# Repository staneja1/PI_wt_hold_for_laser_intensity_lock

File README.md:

# PI with integrator hold for intensity lock

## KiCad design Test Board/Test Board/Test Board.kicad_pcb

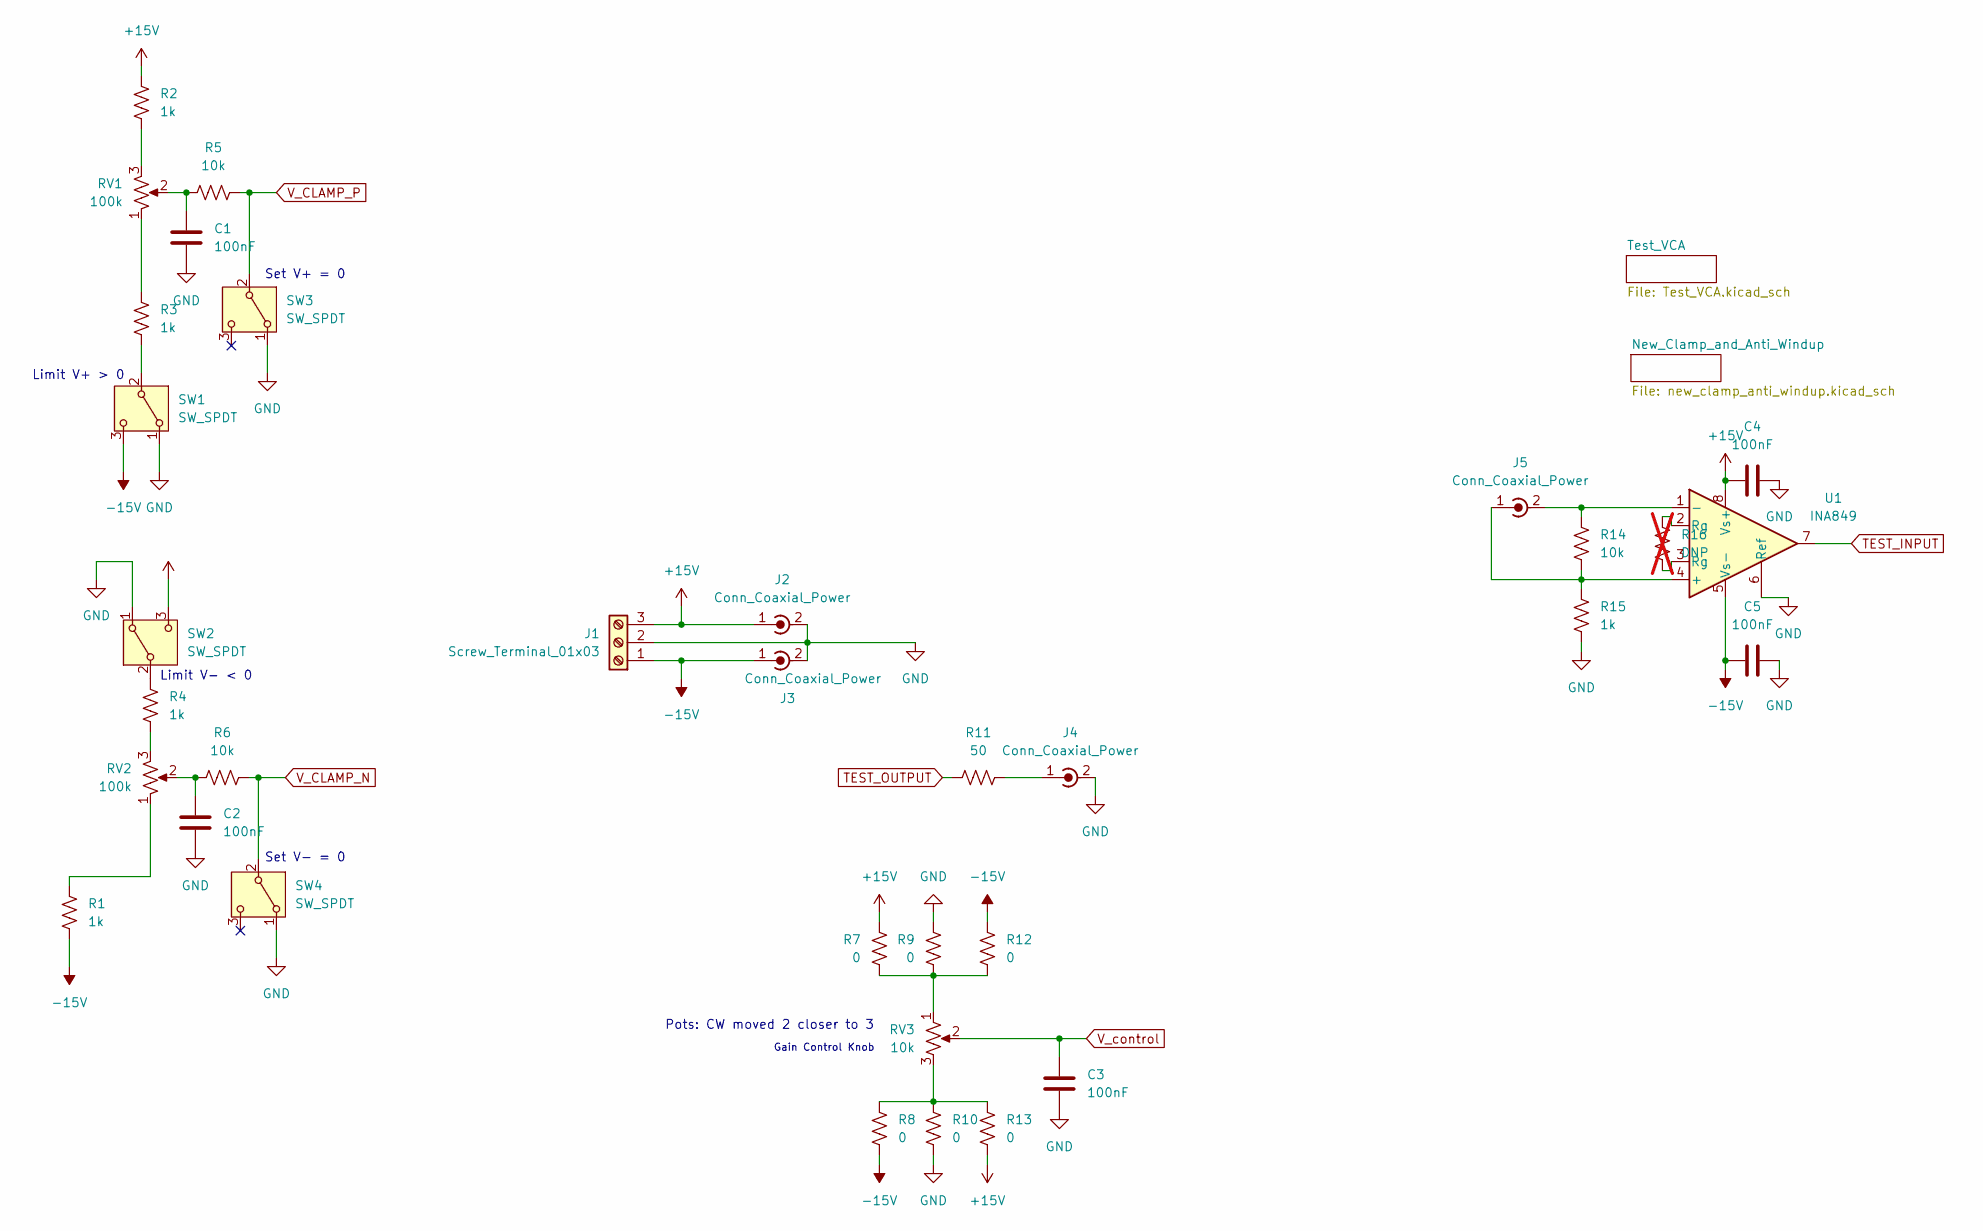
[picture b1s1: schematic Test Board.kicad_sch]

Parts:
C1, C2, C3, C4, C5: 100nF; C_0805_2012Metric; PARTNO CL21B104KCFNNNE; DIGIKEY 1276-6840-1-ND
J1: Screw_Terminal_01x03; TerminalBlock_4Ucon_1x03_P3.50mm_Horizontal; PARTNO 691214110003; DIGIKEY 732-2748-ND
J2, J3, J4, J5: Conn_Coaxial_Power; SMA_Amphenol_901-143_Horizontal
R1, R2, R3, R4: 1k; R_0805_2012Metric
R5, R6, R14: 10k; R_0805_2012Metric; PARTNO RN73H2ATTD1002B25; DIGIKEY 2019-RN73H2ATTD1002B25CT-ND
R7, R8, R9, R10, R12, R13: 0; R_0805_2012Metric; PARTNO CRCW080550R0FKTA; DIGIKEY 541-CRCW080550R0FKTACT-ND
R11: 50; R_0805_2012Metric; PARTNO CRCW080550R0FKTA; DIGIKEY 541-CRCW080550R0FKTACT-ND
R15: 1k; R_0805_2012Metric; PARTNO RG2012P-102-B-T5; DIGIKEY RG20P1.0KBCT-ND
R16: DNP; R_0805_2012Metric; not fitted
RV1, RV2: 100k; Potentiometer_Bourns_3296W_Vertical; PARTNO PV36W104C01B00; DIGIKEY 118-PV36W104C01B00-ND
RV3: 10k; Bourns Circular Pots; PARTNO 3590P-2-104L; DIGIKEY 3590P-2-104L-ND
SW1, SW2, SW3, SW4: SW_SPDT; TDD DIP Switch; PARTNO TDD01H0SB1R; DIGIKEY CKN10546CT-ND
U1: INA849; SOIC-8_3.9x4.9mm_P1.27mm; PARTNO INA849DR; DIGIKEY 296-INA849DRCT-ND

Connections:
+15V: C4.1, J1.3, J2.1 (In), R2.2, R7.2, R13.2, SW2.3 (C), U1.8 (Vs+); also elsewhere on the board
-15V: C5.1, J1.1, J3.1 (In), R1.1, R8.2, R12.2, SW1.3 (C), U1.5 (Vs-); also elsewhere on the board
GND: C1.1, C2.1, C3.1, C4.2, C5.2, J1.2, J2.2 (Ext), J3.2 (Ext), J4.2 (Ext), R9.2, R10.2, R15.1, SW1.1 (A), SW2.1 (A), SW3.1 (A), SW4.1 (A), U1.6 (Ref); also elsewhere on the board
unnamed: C1.2, R5.1, RV1.2
unnamed: C2.2, R6.1, RV2.2
unnamed: J4.1 (In), R11.2
unnamed: J5.2 (Ext), R14.2, U1.1 (-)
unnamed: J5.1 (In), R14.1, R15.2, U1.4 (+)
unnamed: R1.2, RV2.1
unnamed: R2.1, RV1.3
unnamed: R3.2, RV1.1
unnamed: R4.1, RV2.3
unnamed: R8.1, R10.1, R13.1, RV3.3
unnamed: R7.1, R9.1, R12.1, RV3.1
unnamed: R16.1, U1.3 (Rg)
unnamed: R16.2, U1.2 (Rg)
unnamed: R3.1, SW1.2 (B)
unnamed: R4.2, SW2.2 (B)
TEST_INPUT: U1.7; also elsewhere on the board
TEST_OUTPUT: R11.1; also elsewhere on the board
V_CLAMP_N: R6.2, SW4.2 (B); also elsewhere on the board
V_CLAMP_P: R5.2, SW3.2 (B); also elsewhere on the board
V_control: C3.2, RV3.2; also elsewhere on the board

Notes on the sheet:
Limit V+ > 0
Set V+ = 0
Limit V- < 0
Gain Control Knob
Set V- = 0
Pots: CW moved 2 closer to 3

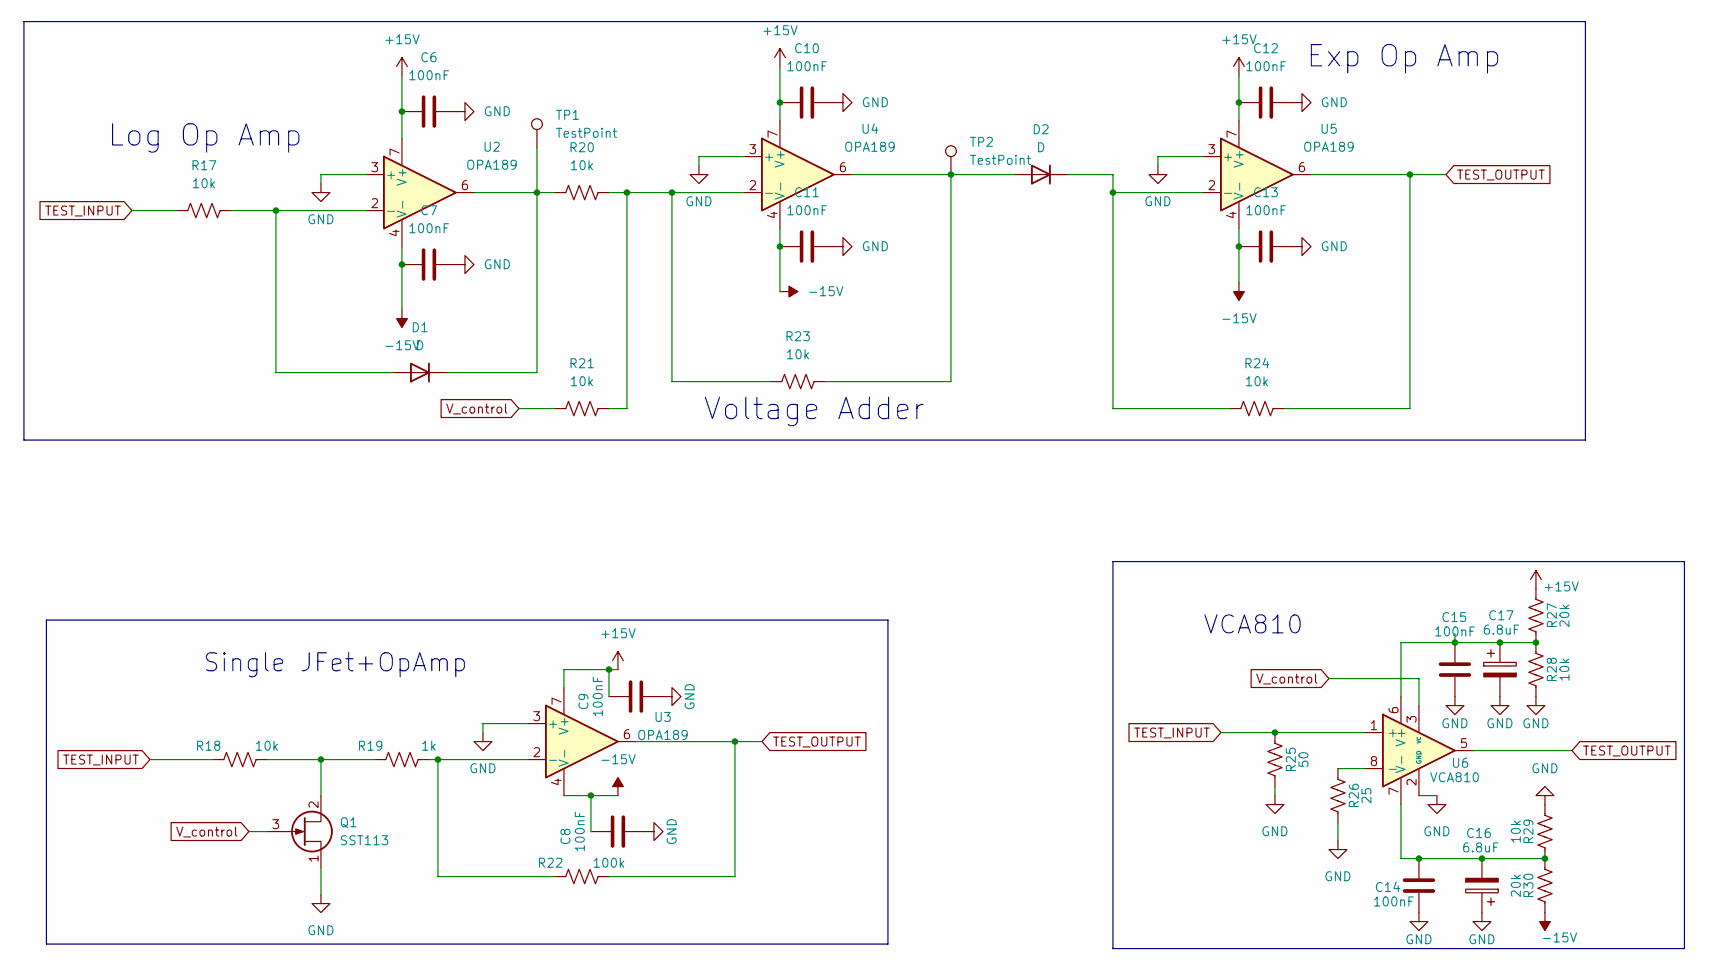
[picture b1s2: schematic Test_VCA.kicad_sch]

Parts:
C6, C7, C8, C9, C10, C11, C12, C13, C14, C15: 100nF; C_0805_2012Metric; PARTNO CL21B104KCFNNNE; DIGIKEY 1276-6840-1-ND
C16, C17: 6.8uF; C_0805_2012Metric
D1, D2: D; TSOT-23; PARTNO SSTPAD5 SOT-23 3L ROHS; DIGIKEY 4004-SSTPAD5SOT-233LROHSCT-ND
Q1: SST113; SOT-23
R17, R18, R23, R24, R28, R29: 10k; R_0805_2012Metric
R19: 1k; R_0805_2012Metric
R20, R21: 10k; R_0805_2012Metric; PARTNO RN73H2ATTD1002B25; DIGIKEY 2019-RN73H2ATTD1002B25CT-ND
R22: 100k; R_0805_2012Metric
R25: 50; R_0805_2012Metric
R26: 25; R_0805_2012Metric
R27, R30: 20k; R_0805_2012Metric
TP1, TP2: TestPoint; TestPoint_Loop_D2.60mm_Drill1.6mm_Beaded
U2, U3, U4, U5: OPA189; SOIC-8_3.9x4.9mm_P1.27mm; PARTNO OPA189ID; DIGIKEY 296-47522-ND
U6: VCA810; SOIC-8_3.9x4.9mm_P1.27mm

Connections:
+15V: C6.1, C9.1, C10.1, C12.1, R27.1, U2.7 (V+), U3.7 (V+), U4.7 (V+), U5.7 (V+); also elsewhere on the board
-15V: C7.1, C8.1, C11.1, C13.1, R30.1, U2.4 (V-), U3.4 (V-), U4.4 (V-), U5.4 (V-); also elsewhere on the board
GND: C6.2, C7.2, C8.2, C9.2, C10.2, C11.2, C12.2, C13.2, C14.2, C15.2, C16.1, C17.2, Q1.1 (S), R25.2, R26.2, R28.2, R29.2, U2.3 (+), U3.3 (+), U4.3 (+), U5.3 (+), U6.2 (GND); also elsewhere on the board
unnamed: D1.2 (A), R17.2, U2.2 (-)
unnamed: D1.1 (K), R20.1, TP1.1 (1_1), U2.6
unnamed: D2.2 (A), R23.2, TP2.1 (1_1), U4.6
unnamed: D2.1 (K), R24.1, U5.2 (-)
unnamed: Q1.2 (D), R18.2, R19.1
unnamed: R19.2, R22.1, U3.2 (-)
unnamed: R20.2, R21.2, R23.1, U4.2 (-)
unnamed: R26.1, U6.8 (-)
unnamed: C15.1, C17.1, R27.2, R28.1, U6.6 (V+)
unnamed: C14.1, C16.2, R29.1, R30.2, U6.7 (V-)
TEST_INPUT: R17.1, R18.1, R25.1, U6.1 (+); also elsewhere on the board
TEST_OUTPUT: R22.2, R24.2, U3.6, U5.6, U6.5; also elsewhere on the board
V_control: Q1.3 (G), R21.1, U6.3 (VC); also elsewhere on the board

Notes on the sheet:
Exp Op Amp
Voltage Adder
Single JFet+OpAmp
VCA810
Log Op Amp

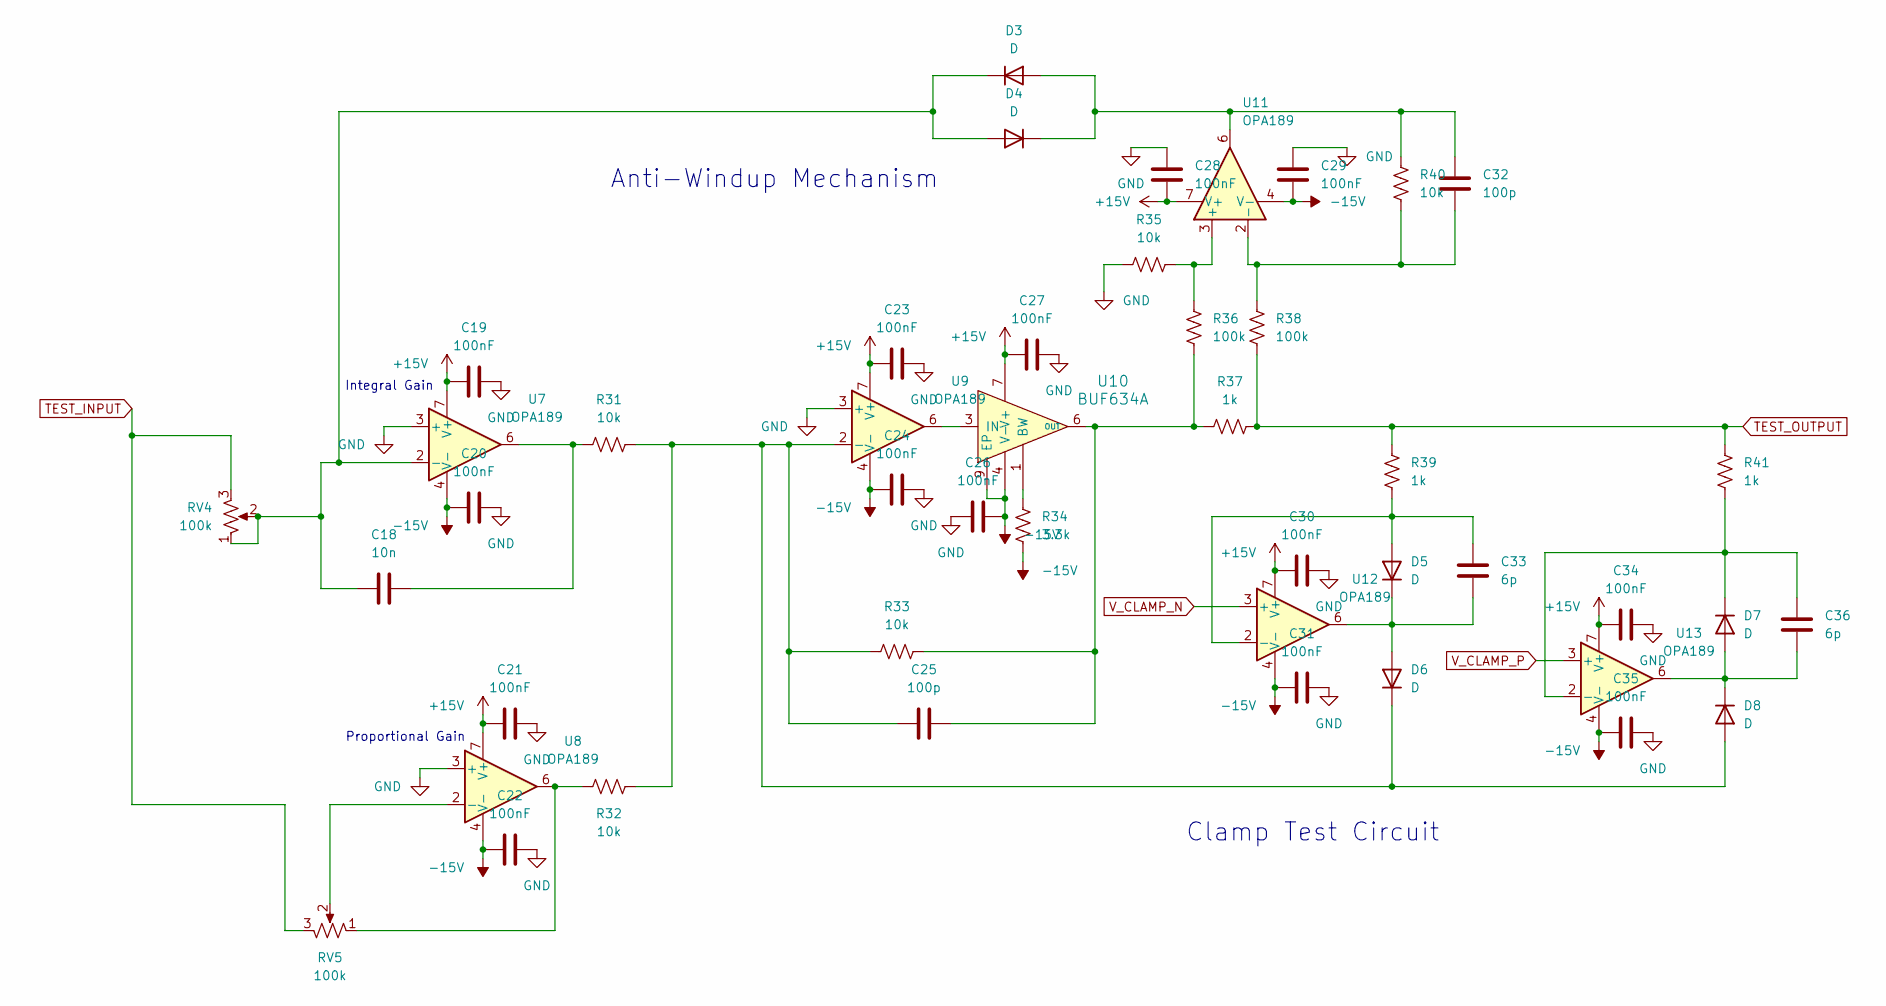
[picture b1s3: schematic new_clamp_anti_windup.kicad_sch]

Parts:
C18: 10n; C_0805_2012Metric; PARTNO C0805C101J5GACTU; DIGIKEY 399-C0805C101J5GACTUCT-ND
C19, C20, C21, C22, C23, C24, C26, C27, C28, C29, C30, C31, C34, C35: 100nF; C_0805_2012Metric; PARTNO CL21B104KCFNNNE; DIGIKEY 1276-6840-1-ND
C25, C32: 100p; C_0805_2012Metric; PARTNO C0805C101J5GACTU; DIGIKEY 399-C0805C101J5GACTUCT-ND
C33, C36: 6p; C_0805_2012Metric
D3, D4, D5, D6, D7, D8: D; TSOT-23; PARTNO SSTPAD5 SOT-23 3L ROHS; DIGIKEY 4004-SSTPAD5SOT-233LROHSCT-ND
R31, R32, R33, R35, R40: 10k; R_0805_2012Metric; PARTNO RN73H2ATTD1002B25; DIGIKEY 2019-RN73H2ATTD1002B25CT-ND
R34: 3.3k; R_0805_2012Metric; PARTNO RC0805FR-073K3L; DIGIKEY 311-3.30KCRCT-ND
R36, R38: 100k; R_0805_2012Metric; PARTNO RN73H2ATTD1002B25; DIGIKEY 2019-RN73H2ATTD1002B25CT-ND
R37, R39, R41: 1k; R_0805_2012Metric; PARTNO RG2012P-102-B-T5; DIGIKEY RG20P1.0KBCT-ND
RV4, RV5: 100k; Potentiometer_Bourns_3296W_Vertical; PARTNO PV36W104C01B00; DIGIKEY 118-PV36W104C01B00-ND
U7, U8, U9, U11, U12, U13: OPA189; SOIC-8_3.9x4.9mm_P1.27mm; PARTNO OPA189ID; DIGIKEY 296-47522-ND
U10: BUF634A; BUF634AIDDAR; PARTNO BUF634AIDDAR; DIGIKEY 296-BUF634AIDDARCT-ND

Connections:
+15V: C19.1, C21.1, C23.1, C27.1, C28.2, C30.1, C34.1, U7.7 (V+), U8.7 (V+), U9.7 (V+), U10.7 (V+), U11.7 (V+), U12.7 (V+), U13.7 (V+); also elsewhere on the board
-15V: C20.1, C22.1, C24.1, C26.2, C29.1, C31.1, C35.1, R34.1, U7.4 (V-), U8.4 (V-), U9.4 (V-), U10.4 (V-), U10.9 (EP), U11.4 (V-), U12.4 (V-), U13.4 (V-); also elsewhere on the board
GND: C19.2, C20.2, C21.2, C22.2, C23.2, C24.2, C26.1, C27.2, C28.1, C29.2, C30.2, C31.2, C34.2, C35.2, R35.2, U7.3 (+), U8.3 (+), U9.3 (+); also elsewhere on the board
unnamed: C18.1, R31.1, U7.6
unnamed: C32.1, D3.2 (A), D4.1 (K), R40.2, U11.6
unnamed: C18.2, D3.1 (K), D4.2 (A), RV4.1, RV4.2, U7.2 (-)
unnamed: C33.1, D5.2 (A), R39.1, U12.2 (-)
unnamed: C33.2, D5.1 (K), D6.2 (A), U12.6
unnamed: C25.2, D6.1 (K), D8.2 (A), R31.2, R32.2, R33.1, U9.2 (-)
unnamed: C36.2, D7.2 (A), D8.1 (K), U13.6
unnamed: C36.1, D7.1 (K), R41.1, U13.2 (-)
unnamed: R32.1, RV5.1, U8.6
unnamed: RV5.2, U8.2 (-)
unnamed: R34.2, U10.1 (BW)
unnamed: U9.6, U10.3 (IN)
unnamed: C25.1, R33.2, R36.1, R37.2, U10.6 (OUT)
unnamed: R35.1, R36.2, U11.3 (+)
unnamed: C32.2, R38.2, R40.1, U11.2 (-)
TEST_INPUT: RV4.3, RV5.3; also elsewhere on the board
TEST_OUTPUT: R37.1, R38.1, R39.2, R41.2; also elsewhere on the board
V_CLAMP_N: U12.3 (+); also elsewhere on the board
V_CLAMP_P: U13.3 (+); also elsewhere on the board

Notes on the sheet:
Clamp Test Circuit
Proportional Gain
Anti-Windup Mechanism
Integral Gain

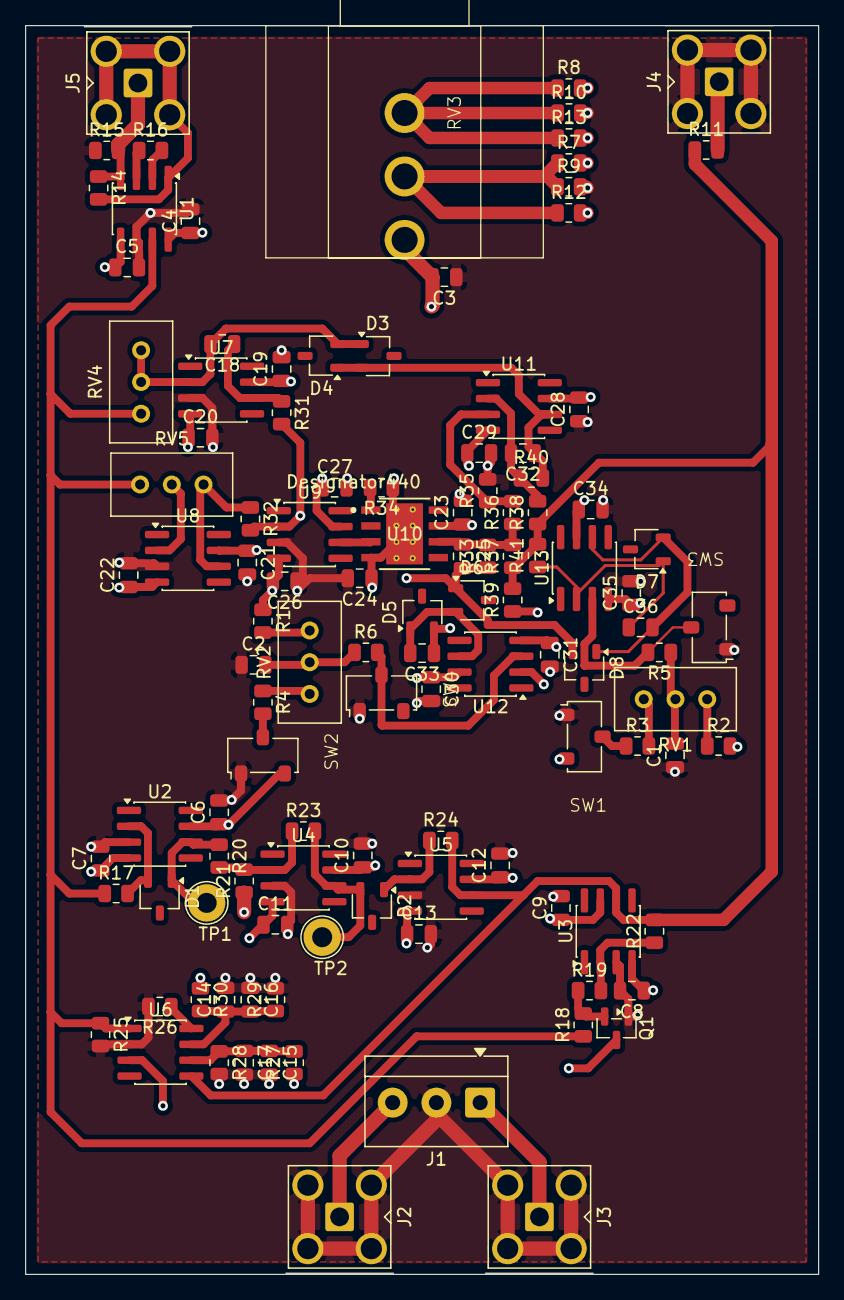
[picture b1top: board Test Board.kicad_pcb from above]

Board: 4 copper layers, 63.5 x 100.0 mm, 115 parts (0 on the bottom side), 48 nets.

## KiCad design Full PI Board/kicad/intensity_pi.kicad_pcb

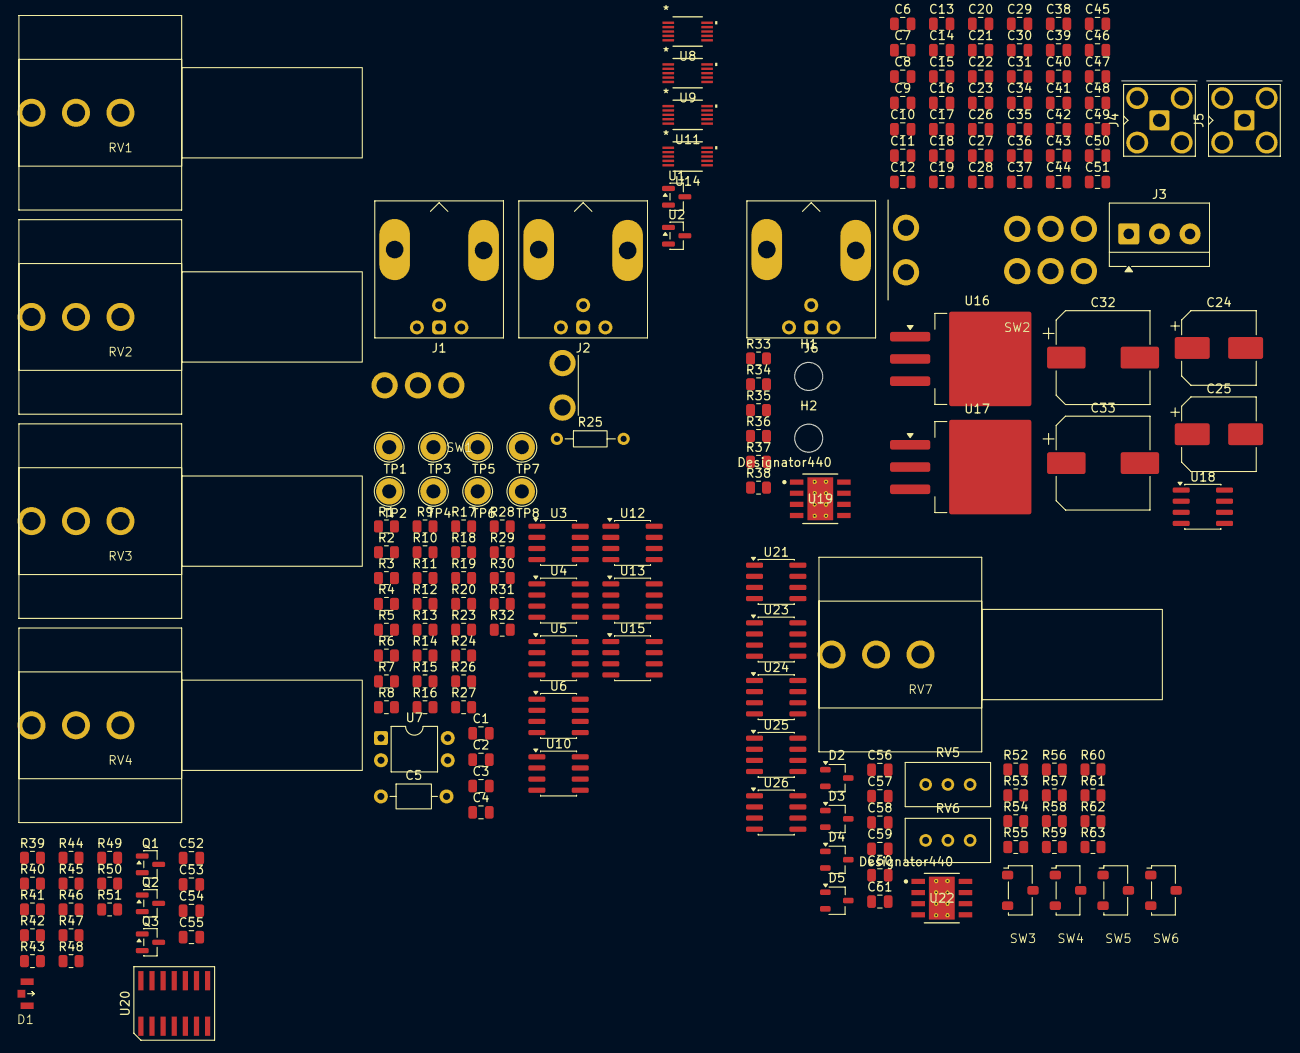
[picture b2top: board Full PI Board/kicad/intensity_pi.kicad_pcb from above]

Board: 4 copper layers, 185 parts (0 on the bottom side), 85 nets, no tracks yet.

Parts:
C1, C2, C14, C15, C16, C17, C18, C19, C20, C21, C22, C23, C26, C27, C28, C29, C30, C31, C34, C35, C36, C37, C38, C39, C40, C41, C42, C43, C44, C45, C46, C47, C48, C49, C50, C51, C52, C53, C54, C55, C56, C58, C60: 100nF; C_0805_2012Metric
C3: C; C_0805_2012Metric
C4: 10nF; C_0805_2012Metric
C5: C; C_Axial_L3.8mm_D2.6mm_P7.50mm_Horizontal
C6, C7, C8, C9, C10, C11, C12, C13: 1uF; C_0805_2012Metric
C24, C25: 100uF; CP_Elec_8x6.5
C32, C33: 220uF; CP_Elec_10x10.5
C57: 100p; C_0805_2012Metric
C59, C61: 6p; C_0805_2012Metric
D1: LED_Dual_KKA; GR LED
D2, D3, D4, D5: D; TSOT-23
H1, H2: MountingHole; MountingHole_3.2mm_M3_ISO14580
J1, J2, J6: Conn_Coaxial_x2_Isolated; BNC_Amphenol_031-6575_Horizontal
J3: Screw_Terminal_01x03; TerminalBlock_4Ucon_1x03_P3.50mm_Horizontal
J4, J5: Conn_Coaxial_Power; SMA_Amphenol_901-143_Horizontal
Q1, Q2, Q3: 2N7002E; SOT-23
R1, R2, R3, R5, R7, R10, R13, R14, R16, R17, R18, R20, R27, R28, R29, R30, R31, R32, R43, R45, R46, R48, R54, R55, R57, R59: 10k; R_0805_2012Metric
R4, R6, R8, R19, R24, R33, R34, R35, R36, R51, R52, R53, R56, R58, R61, R62: 1k; R_0805_2012Metric
R9, R11, R12: DNP; R_0805_2012Metric
R15: 180; R_0805_2012Metric
R23: 50k; R_0805_2012Metric
R25: R_Axial_DIN0204_L3.6mm_D1.6mm_P7.62mm_Horizontal
R26: 1M; R_0805_2012Metric
R37, R60: 3.3k; R_0805_2012Metric
R38, R63: 50; R_0805_2012Metric
R39, R42: 40k; R_0805_2012Metric
R40, R41: 5k; R_0805_2012Metric
R44: 80k; R_0805_2012Metric
R47, R49, R50: 100; R_0805_2012Metric
RV1, RV2, RV3, RV4, RV7: 100k; Bourns Circular Pots
RV5, RV6: 100k; Potentiometer_Bourns_3296W_Vertical
SW1: SW_SPDT; Right Angle SPDT Vertical
SW2: SW_SP3T; Right Angle SP3T Vertical
SW3, SW4, SW5, SW6: SW_SPDT; TDD DIP Switch
TP1, TP2, TP3, TP4, TP5, TP6, TP7, TP8: TestPoint; TestPoint_Loop_D2.60mm_Drill1.6mm_Beaded
U1, U2: LM4040DBZ-5; SOT-23
U3, U4, U5: INA849; SOIC-8_3.9x4.9mm_P1.27mm
U6, U10, U12, U13, U15, U18, U21, U23, U24, U25, U26: OPA189; SOIC-8_3.9x4.9mm_P1.27mm
U7: PC817; DIP-4_W7.62mm
U8, U9: TMUX6123
U11, U14: TMUX6121
U16: L7815; TO-263-3_TabPin2
U17: L7915; TO-263-3_TabPin2
U19, U22: BUF634A; BUF634AIDDAR
U20: 4x Comparator; SOIC-14

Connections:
+15V: C6.1, C8.1, C10.1, C12.1, C14.1, C16.1, C18.1, C20.1, C22.1, C26.1, C28.1, C30.1, C32.1, C34.1, C36.1, C38.1, C40.1, C42.1, C44.1, C46.1, C48.1, C50.1, R1.2, R19.1, R39.2, R46.2, R48.2, R51.1, R52.2, SW2.3, SW5.3 (C), U3.8 (Vs+), U4.8 (Vs+), U5.8 (Vs+), U6.7 (V+), U8.9 (VDD), U9.9 (VDD), U10.7 (V+), U11.9 (VDD), U12.7 (V+), U13.7 (V+), U14.9 (VDD), U15.7 (V+), U16.3 (OUT), U18.7 (V+), U19.7 (V+), U20.3 (V+), U21.7 (V+), U22.7 (V+), U23.7 (V+), U24.7 (V+), U25.7 (V+), U26.7 (V+)
+V_DC_unregulated: C24.1, J3.3, J4.1 (In), U16.1 (IN)
-15V: C7.2, C9.2, C11.2, C13.2, C15.2, C17.2, C19.2, C21.2, C23.2, C27.2, C29.2, C31.2, C33.2, C35.2, C37.2, C39.2, C41.2, C43.2, C45.2, C47.2, C49.2, C51.2, R2.1, R37.1, R42.1, R56.1, R60.1, SW3.3 (C), U3.5 (Vs-), U4.5 (Vs-), U5.5 (Vs-), U6.4 (V-), U8.6 (VSS), U9.6 (VSS), U10.4 (V-), U11.6 (VSS), U12.4 (V-), U13.4 (V-), U14.2, U14.6 (VSS), U15.4 (V-), U17.3 (VO), U18.4 (V-), U19.4 (V-), U19.9 (EP), U20.12 (V-), U21.4 (V-), U22.4 (V-), U22.9 (EP), U23.4 (V-), U24.4 (V-), U25.4 (V-), U26.4 (V-)
-V_DC_unregulated: C25.2, J3.1, J5.1 (In), U17.2 (VI)
Error_signal: R20.1, R36.2, RV3.3, RV4.3, TP4.1 (1_1), U10.6, U20.9 (+), U20.10 (-)
GND: C1.1, C6.2, C7.1, C8.2, C9.1, C10.2, C11.1, C12.2, C13.1, C14.2, C15.1, C16.2, C17.1, C18.2, C19.1, C20.2, C21.1, C22.2, C23.1, C24.2, C25.1, C26.2, C27.1, C28.2, C29.1, C30.2, C31.1, C32.2, C33.1, C34.2, C35.1, C36.2, C37.1, C38.2, C39.1, C40.2, C41.1, C42.2, C43.1, C44.2, C45.1, C46.2, C47.1, C48.2, C49.1, C50.2, C51.1, C52.1, C53.1, C54.1, C55.1, C56.1, C58.1, C60.1, J3.2, J4.2 (Ext), J5.2 (Ext), J6.2 (Ext1), J6.4 (Ext2), Q1.2 (S), Q2.2 (S), Q3.2 (S), R4.1, R6.1, R8.1, R13.1, R31.2, R33.2, R34.2, R35.2, R40.1, R41.2, RV2.3, SW1.2 (B), SW3.1 (A), SW4.1 (A), SW5.1 (A), SW6.1 (A), U1.2 (A), U2.1 (K), U3.6 (Ref), U4.6 (Ref), U5.6 (Ref), U7.3, U8.8 (GND), U9.2, U9.8 (GND), U11.8 (GND), U12.3 (+), U13.3 (+), U14.8 (GND), U16.2 (GND), U17.1 (GND), U21.3 (+)
Input_A: R16.1, TP2.1 (1_1), U4.7
Internal_setpoint: C2.1, R14.2, R18.1, TP1.1 (1_1), U6.6
LFGL: R34.1, SW2.2, U11.10 (SEL2)
LOCK_OFF: R33.1, SW2.1, U11.1 (SEL1), U14.1 (SEL1), U14.10 (SEL2)
LOCK_ON: R35.1, SW2.4
unnamed: C1.2, R10.1, RV1.2
unnamed: C3.1, U9.3, U9.4
unnamed: C3.2, R24.2
unnamed: C56.2, R55.1, RV5.2
unnamed: C58.2, R59.1, RV6.2
unnamed: D1.3 (A), R51.2
unnamed: D1.1 (K1), Q3.3 (D)
unnamed: D1.2 (K2), Q2.3 (D)
unnamed: C59.1, D2.2 (A), R61.1, U23.2 (-)
unnamed: C59.2, D2.1 (K), D3.2 (A), U23.6
unnamed: C57.2, D3.1 (K), D5.2 (A), R54.2, R57.1, U21.2 (-)
unnamed: C61.2, D4.2 (A), D5.1 (K), U26.6
unnamed: C61.1, D4.1 (K), R62.1, U26.2 (-)
unnamed: J1.2 (Ext1), R5.2, U5.4 (+)
unnamed: J1.1 (In1), R5.1, R6.2, U5.1 (-)
unnamed: J1.4 (Ext2), R7.2, U4.1 (-)
unnamed: J1.3 (In2), R7.1, R8.2, U4.4 (+)
unnamed: J2.2 (Ext1), R3.2, U3.4 (+)
unnamed: J2.1 (In1), R3.1, R4.2, U3.1 (-)
unnamed: J2.4 (Ext2), U7.2
unnamed: J2.3 (In2), R15.2
unnamed: J6.1 (In1), R63.2
unnamed: J6.3 (In2), R38.2
unnamed: Q1.3 (D), R48.1, R50.2
unnamed: Q1.1 (G), R47.2
unnamed: Q2.1 (G), R49.2
unnamed: Q3.1 (G), R50.1
unnamed: R9.1, U3.3 (Rg)
unnamed: R9.2, U3.2 (Rg)
unnamed: R11.1, U4.3 (Rg)
unnamed: R11.2, U4.2 (Rg)
unnamed: R12.1, U5.3 (Rg)
unnamed: R12.2, U5.2 (Rg)
unnamed: R15.1, U7.1
unnamed: R17.1, U5.7
unnamed: R23.2, R29.1, TP7.1 (1_1), U8.5, U13.6, U14.5
unnamed: R25.1, R26.1, U11.5
unnamed: R46.1, R47.1, R49.1, U14.3, U20.1, U20.2, U20.13, U20.14
unnamed: R52.1, RV5.3
unnamed: R53.2, RV5.1
unnamed: R56.2, RV6.1
unnamed: R58.1, RV6.3
unnamed: RV2.1, U3.7
unnamed: RV3.1, RV3.2, U8.2
unnamed: R10.2, SW1.1 (A), U6.3 (+)
unnamed: R53.1, SW3.2 (B)
unnamed: R58.2, SW5.2 (B)
unnamed: R1.1, RV1.3, U1.1 (K)
unnamed: R2.2, RV1.1, U2.2 (A)
unnamed: C2.2, R13.2, R14.1, U6.2 (-)
unnamed: R19.2, U7.4, U8.1 (SEL1), U8.10 (SEL2), U9.1 (SEL1), U9.10 (SEL2)
unnamed: R16.2, R17.2, R18.2, U10.3 (+)
unnamed: R20.2, U10.2 (-)
unnamed: R23.1, RV4.1, RV4.2, U8.4, U13.2 (-), U14.4
unnamed: R27.2, R28.2, R29.2, R30.2, U15.3 (+)
unnamed: R32.2, U15.2 (-)
unnamed: R36.1, U18.3 (+)
unnamed: R38.1, U18.2 (-), U19.6 (OUT)
unnamed: R37.2, U19.1 (BW)
unnamed: U18.6, U19.3 (IN)
unnamed: C54.2, R43.1, R44.2, U20.5 (+)
unnamed: C55.2, R44.1, R45.2, U20.6 (-)
unnamed: C53.2, R41.1, R42.2, U20.8 (-)
unnamed: C52.2, R39.1, R40.2, U20.11 (+)
unnamed: R60.2, U22.1 (BW)
unnamed: U21.6, U22.3 (IN)
unnamed: C57.1, R57.2, R61.2, R62.2, R63.1, U22.6 (OUT)
unnamed: RV7.3, U24.2 (-), U24.6
unnamed: RV7.1, U25.2 (-), U25.6
OUTPUT_OFFSET: C60.2, R30.1, R31.1, RV7.2, TP8.1 (1_1)
Sweep_IN: R28.1, RV2.2, TP5.1 (1_1)
V_CLAMP_N: R45.1, R59.2, SW6.2 (B), U23.3 (+), U25.3 (+)
V_CLAMP_P: R43.2, R55.2, SW4.2 (B), U24.3 (+), U26.3 (+)
V_PI_OUT: R32.1, R54.1, U15.6, U20.4 (-), U20.7 (+)

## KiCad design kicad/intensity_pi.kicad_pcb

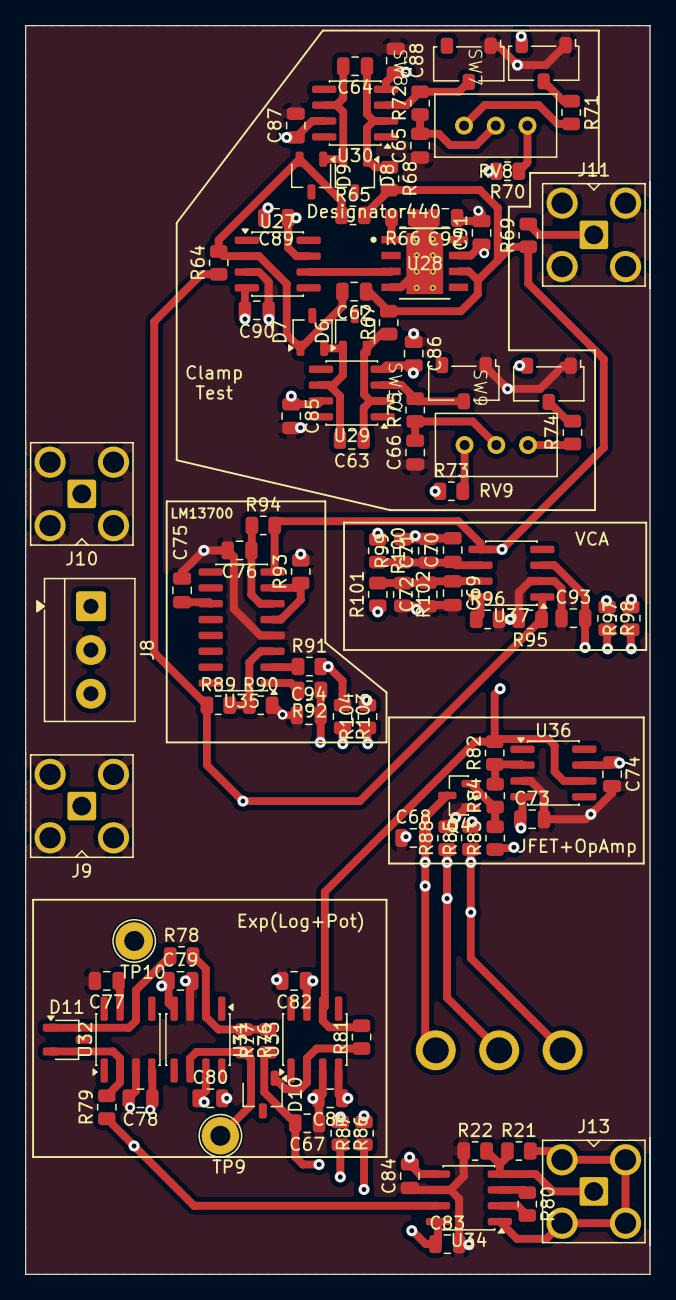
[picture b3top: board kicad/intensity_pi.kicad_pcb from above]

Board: 4 copper layers, 50.0 x 100.0 mm, 108 parts (1 on the bottom side), 44 nets.

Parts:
C62: 100p; C_0805_2012Metric
C63, C64: 6p; C_0805_2012Metric
C65, C66, C67, C68, C69, C70, C73, C74, C75, C76, C77, C78, C79, C80, C81, C82, C83, C84, C85, C86, C87, C88, C89, C90, C91, C92, C93, C94: 100nF; C_0805_2012Metric
C71, C72: 6.8uF; C_0805_2012Metric
D6, D7, D8, D9, D10, D11: D; TSOT-23
J8: Screw_Terminal_01x03; TerminalBlock_4Ucon_1x03_P3.50mm_Horizontal
J9, J10, J11, J13: Conn_Coaxial_Power; SMA_Amphenol_901-143_Horizontal
Q4: SST113; SOT-23
R21, R64, R65, R72, R75, R76, R77, R78, R79, R81, R99, R102: 10k; R_0805_2012Metric
R22, R67, R68, R70, R71, R73, R74, R82, R90: 1k; R_0805_2012Metric
R66: 3.3k; R_0805_2012Metric
R69, R95: 50; R_0805_2012Metric
R80: DNP; R_0805_2012Metric
R83: 10; R_0805_2012Metric
R84: 100; R_0805_2012Metric
R85: 400k; R_0805_2012Metric
R86, R87, R88, R97, R103, R104: 0; R_0805_2012Metric
R89, R92, R93: 30k; R_0805_2012Metric
R91: 13k; R_0805_2012Metric
R94: 5k; R_0805_2012Metric
R96: 25; R_0805_2012Metric
R98: 650k; R_0805_2012Metric
R100, R101: 20k; R_0805_2012Metric
RV8, RV9: 100k; Potentiometer_Bourns_3296W_Vertical
RV10: 100k; Bourns Circular Pots
SW7, SW8, SW9, SW10: SW_SPDT; TDD DIP Switch
TP9, TP10: TestPoint; TestPoint_Loop_D2.60mm_Drill1.6mm_Beaded
U27, U29, U30, U31, U32, U33, U36: OPA189; SOIC-8_3.9x4.9mm_P1.27mm
U28: BUF634A; BUF634AIDDAR
U34: INA849; SOIC-8_3.9x4.9mm_P1.27mm
U35: LM13700; SOIC-16_3.9x9.9mm_P1.27mm
U37: VCA810; SOIC-8_3.9x4.9mm_P1.27mm

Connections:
+15V_TEST: C74.1, C75.1, C77.1, C80.1, C82.1, C83.1, C85.1, C87.1, C89.1, C91.1, J8.3, J9.1 (In), R70.2, R86.1, R91.2, R100.1, R103.1, SW9.3 (C), U27.7 (V+), U28.7 (V+), U29.7 (V+), U30.7 (V+), U31.7 (V+), U32.7 (V+), U33.7 (V+), U34.8 (Vs+), U35.11 (V+), U36.7 (V+)
-15V_TEST: C73.1, C76.1, C78.1, C79.1, C81.1, C84.2, C86.2, C88.2, C90.2, C92.2, J8.1, J10.1 (In), R66.1, R73.1, R85.2, R87.2, R94.1, R98.1, R101.1, R104.2, SW7.3 (C), U27.4 (V-), U28.4 (V-), U28.9 (EP), U29.4 (V-), U30.4 (V-), U31.4 (V-), U32.4 (V-), U33.4 (V-), U34.5 (Vs-), U35.6 (V-), U36.4 (V-)
GND: C65.1, C66.1, C67.1, C68.1, C69.2, C70.2, C71.2, C72.1, C73.2, C74.2, C75.2, C76.2, C77.2, C78.2, C79.2, C80.2, C81.2, C82.2, C83.2, C84.1, C85.2, C86.1, C87.2, C88.1, C89.2, C90.1, C91.2, C92.1, C93.1, C94.1, J8.2, J9.2 (Ext), J10.2 (Ext), J11.2 (Ext), Q4.1 (S), R22.1, R88.2, R90.2, R93.2, R95.2, R96.2, R97.2, R99.2, R102.2, SW7.1 (A), SW8.1 (A), SW9.1 (A), SW10.1 (A), U27.3 (+), U31.3 (+), U32.3 (+), U33.3 (+), U34.6 (Ref), U35.4 (-), U36.3 (+), U37.2 (GND)
unnamed: C65.2, R72.1, RV8.2
unnamed: C66.2, R75.1, RV9.2
unnamed: C63.1, D6.2 (A), R67.1, U29.2 (-)
unnamed: C63.2, D6.1 (K), D7.2 (A), U29.6
unnamed: C62.2, D7.1 (K), D9.2 (A), R64.2, R65.1, U27.2 (-)
unnamed: C64.2, D8.2 (A), D9.1 (K), U30.6
unnamed: C64.1, D8.1 (K), R68.1, U30.2 (-)
unnamed: D10.2 (A), R76.2, TP9.1 (1_1), U31.6
unnamed: D10.1 (K), R81.1, U33.2 (-)
unnamed: D11.2 (A), R79.2, U32.2 (-)
unnamed: D11.1 (K), R78.1, TP10.1 (1_1), U32.6
unnamed: J11.1 (In), R69.2
unnamed: J13.2 (Ext), R21.2, U34.1 (-)
unnamed: J13.1 (In), R21.1, R22.2, U34.4 (+)
unnamed: Q4.2 (D), R83.2, R84.1
unnamed: R70.1, RV8.3
unnamed: R71.2, RV8.1
unnamed: R73.2, RV9.1
unnamed: R74.1, RV9.3
unnamed: R80.1, U34.3 (Rg)
unnamed: R80.2, U34.2 (Rg)
unnamed: R92.2, U35.1
unnamed: R93.1, U35.5, U35.7
unnamed: R71.1, SW7.2 (B)
unnamed: R74.2, SW9.2 (B)
unnamed: R66.2, U28.1 (BW)
unnamed: U27.6, U28.3 (IN)
unnamed: R76.1, R77.2, R78.2, U31.2 (-)
unnamed: R89.2, R90.1, U35.3 (+)
unnamed: R91.1, U35.2 (DIODE_BIAS)
unnamed: R82.1, R84.2, U36.2 (-)
unnamed: R96.1, U37.8 (-)
unnamed: C70.1, C71.1, R99.1, R100.2, U37.6 (V+)
unnamed: C69.1, C72.2, R101.2, R102.1, U37.7 (V-)
POT_1_TEST: R86.2, R88.1, R98.2, R103.2, RV10.1
POT_2_TEST: C67.2, C68.2, C93.2, C94.2, Q4.3 (G), R77.1, R92.1, RV10.2, U37.3 (VC)
POT_3_TEST: R85.1, R87.1, R97.1, R104.1, RV10.3
TEST_INPUT: R64.1, R79.1, R83.1, R89.1, R95.1, U34.7, U37.1 (+)
TEST_OUTPUT: C62.1, R65.2, R67.2, R68.2, R69.1, R81.2, R82.2, R94.2, U28.6 (OUT), U33.6, U35.8, U36.6, U37.5
V_CLAMP_N_TEST: R75.2, SW10.2 (B), U29.3 (+)
V_CLAMP_P_TEST: R72.2, SW8.2 (B), U30.3 (+)

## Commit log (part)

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2025-06-30 Importing unfinished project files from archive
2025-06-30 Updated Schematic, removed sw1,2,3a,4, have to fix 3a for zero offset switch
2025-07-02 Finished Cleaning up Schematic, TODO: Add LED and pick parts
2025-07-02 Cleaned up PCB, custom footprint for switch
2025-07-03 Added all features to schematic, TODO: fix pot footprint and layout pcb
2025-07-04 Finished Schematic and Assigning Footprint pending Review, TODO: Layout Board
2025-07-04 First portion of routing
2025-07-07 Updates to PCB placement, removed one extra capacitor pair
2025-07-07 Fixed Error Threshold Control, replaced 2x optocouplers with transistors, added power rectification + regulators for 15VAC to +- 15VDC, finished pcb routing, TODO: Check all components have parts, ch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
2025-07-08 Fixed LED Threshold schematic, added second power input screw terminal, first attempt at final placement and routing
2025-07-08 Updated some part numbers
2025-07-09 Removed large cap and rectifier, added transistor resistors
2025-07-11 Final Schematic, Reworking PCB pt 1
2025-07-14 Condensed Layout, Removed 5V supply, Shortened Board
2025-07-14 Further improvements to layout, reduce potential for crosstalk
2025-07-15 Rearranged Edge Componenets, simpler board, wider but shorter depth
2025-07-15 Further Layout Refinements
2025-07-17 Added 1k resistor to monitor, TODO: check BOM, reorg PI+LFGL, check power planes/return path, move A,B closer to PI, compress vertically
2025-07-18 Updated Design, more compact layout, precise location values for I/O, Fixed TrimPot footprint, TODO: Finalize BOM, add partnos for SMD R/Cs
2025-07-18 Minor Layout updates, replaced old component part no's, added part no's for rest of parts
2025-07-20 Minor Updates to layout, TODO: Redo PI layout
2025-07-20 Reworked PI control layout, minimize feedback loop size
2025-07-21 Updated PI control Layout, fixed circular pot footprint so that CW rotation decreases R
2025-07-22 Revert change to Library Footprint for switch, update schematic to use resistance between pins 2,3 as starting at maximum, decreasing down on CW rotation
2025-07-23 Connected other leg of Pots, added 3d models from manufacturer for switch+pots
2025-07-24 Fixed Digikey Part numbers for some parts, confirmed final BOM, Fixed Switch Footprint hole size
2025-07-24 Small Routing Changes, Fix Silkscreen part references
2025-07-24 Minor routing improvements
2025-07-26 Removal of antennas and other changes
    The following edits has been made:
    1) Simplification of certain critical traces
    2) Removal of all antennas. Antennas are large traces connected to high
    impedance nodes. I'm quite strict about what high impedance means.
    Anything larger than a few Ohm can be considered high impedance.
    3) Added labels most silkscreen labels where outside the physical board
2025-07-28 fixing missing traces and adding additional vias
2025-10-14 V1.1, Fixedincorrect footprints for Green/Red LED, Diodes, Mosfets, Flipped Input A/B Polarity, Potentiometer labels, Incorrect part nos for V regulators. No functionality changes
2025-10-20 First pass at schematic for updated bidirectional clamping and output offset when the lock is turned off, no layout changes yet
2025-10-20 Remove ground in between P and N clamps, as they can be the same sign
2026-05-31 Updated schematic and design
2026-05-31 add gitignore file
2026-06-02 First pass at updated schematic and loose PCB grouping, TODO: Fix PI Gain values
2026-06-30 Added Test Board to test various gain control as well as clamping mechanism
